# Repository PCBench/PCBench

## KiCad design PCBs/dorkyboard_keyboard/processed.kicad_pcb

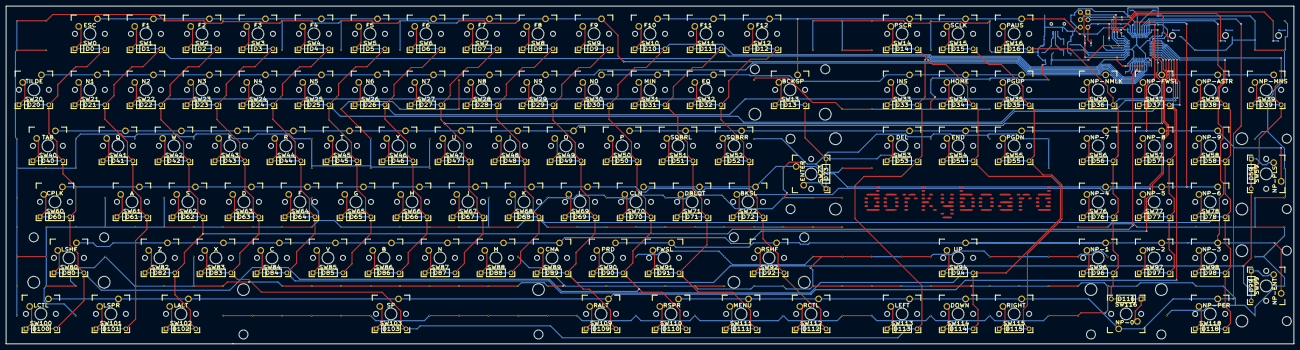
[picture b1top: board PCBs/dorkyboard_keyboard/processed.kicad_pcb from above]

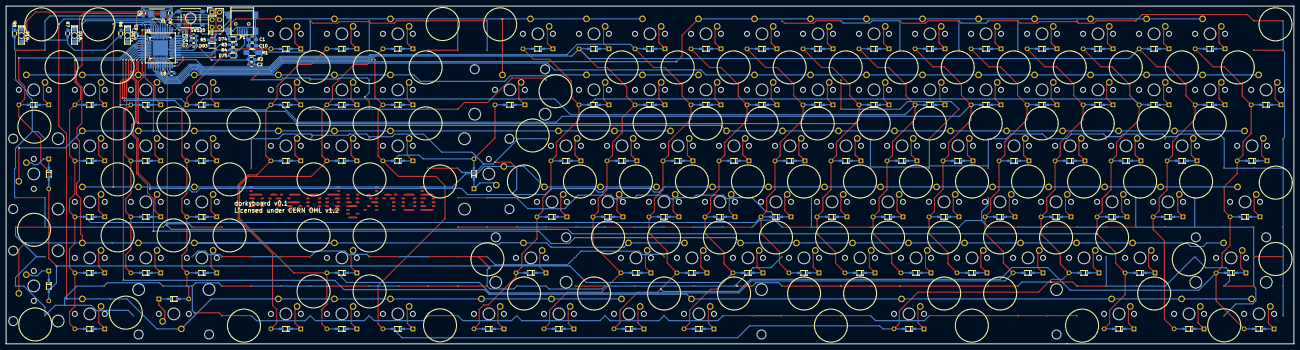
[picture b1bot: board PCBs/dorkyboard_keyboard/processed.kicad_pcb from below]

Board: 2 copper layers, 436.8 x 114.6 mm, 237 parts (29 on the bottom side), 146 nets.

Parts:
C1, C10: 10uF; C_0805_HandSoldering
C2, C3, C4, C8: 100nF; C_0603_HandSoldering
C5, C6: 22pF; C_0603_HandSoldering
C7, C9: 1uF; C_0603_HandSoldering
D0, D1, D2, D3, D4, D5, D6, D7, D8, D9, D10, D11, D12, D13, D14, D15, D16, D20, D21, D22, D23, D24, D25, D26, D27, D28, D29, D30, D31, D32, D33, D34, D35, D36, D37, D38, D39, D40, D41, D42, D43, D44, D45, D46, D47, D48, D49, D50, D51, D52, D53, D54, D55, D56, D57, D58, D59, D60, D61, D62, D63, D64, D65, D66, D67, D68, D69, D70, D71, D72, D73, D76, D77, D78, D80, D82, D83, D84, D85, D86, D87, D88, D89, D90, D91, D92, D94, D96, D97, D98, D99, D100, D101, D102, D103, D109, D110, D111, D112, D113, D114, D115, D116, D118: D_Small; DIODE_TH-SMT
D17, D18, D19: Led_Small; LED Reverse Mount 3.2x1.6mm Dialight
D74, D75: 6.2V; SOD-323_HandSoldering
D93: 1N4148; SOD-323
P1: USB_MiniB; USB_Mini-B
P2: Do Not Populate; Pin_Header_Straight_2x03
R1: 10R Fusible; R_1206_HandSoldering
R2, R5: 10k; R_0603_HandSoldering
R3, R4: 22R; R_0603_HandSoldering
R6, R7, R8: 604R; R_0603_HandSoldering
SW0: ESC; CHERRY_PCB_100H
SW1: F1; CHERRY_PCB_100H
SW2: F2; CHERRY_PCB_100H
SW3: F3; CHERRY_PCB_100H
SW4: F4; CHERRY_PCB_100H
SW5: F5; CHERRY_PCB_100H
SW6: F6; CHERRY_PCB_100H
SW7: F7; CHERRY_PCB_100H
SW8: F8; CHERRY_PCB_100H
SW9: F9; CHERRY_PCB_100H
SW10: F10; CHERRY_PCB_100H
SW11: F11; CHERRY_PCB_100H
SW12: F12; CHERRY_PCB_100H
SW13: BCKSP; CHERRY_PCB_200H
SW14: PSCR; CHERRY_PCB_100H
SW15: SCLK; CHERRY_PCB_100H
SW16: PAUS; CHERRY_PCB_100H
SW20: TILDE; CHERRY_PCB_100H
SW21: N1; CHERRY_PCB_100H
SW22: N2; CHERRY_PCB_100H
SW23: N3; CHERRY_PCB_100H
SW24: N4; CHERRY_PCB_100H
SW25: N5; CHERRY_PCB_100H
SW26: N6; CHERRY_PCB_100H
SW27: N7; CHERRY_PCB_100H
SW28: N8; CHERRY_PCB_100H
SW29: N9; CHERRY_PCB_100H
SW30: N0; CHERRY_PCB_100H
SW31: MIN; CHERRY_PCB_100H
SW32: EQ; CHERRY_PCB_100H
SW33: INS; CHERRY_PCB_100H
SW34: HOME; CHERRY_PCB_100H
SW35: PGUP; CHERRY_PCB_100H
SW36: NP-NMLK; CHERRY_PCB_100H
SW37: NP-FWSL; CHERRY_PCB_100H
SW38: NP-ASTR; CHERRY_PCB_100H
SW39: NP-MNS; CHERRY_PCB_100H
SW40: TAB; CHERRY_PCB_150H
SW41: Q; CHERRY_PCB_100H
SW42: W; CHERRY_PCB_100H
SW43: E; CHERRY_PCB_100H
SW44: R; CHERRY_PCB_100H
SW45: T; CHERRY_PCB_100H
SW46: Y; CHERRY_PCB_100H
SW47: U; CHERRY_PCB_100H
SW48: I; CHERRY_PCB_100H
SW49: O; CHERRY_PCB_100H
SW50: P; CHERRY_PCB_100H
SW51: SQBRL; CHERRY_PCB_100H
SW52: SQBRR; CHERRY_PCB_100H
SW53: DEL; CHERRY_PCB_100H
SW54: END; CHERRY_PCB_100H
SW55: PGDN; CHERRY_PCB_100H
SW56: NP-7; CHERRY_PCB_100H
SW57: NP-8; CHERRY_PCB_100H
SW58: NP-9; CHERRY_PCB_100H
SW59: NP-PLS; CHERRY_PCB_200V
SW60: CPLK; CHERRY_PCB_175H
SW61: A; CHERRY_PCB_100H
SW62: S; CHERRY_PCB_100H
SW63: D; CHERRY_PCB_100H
SW64: F; CHERRY_PCB_100H
SW65: G; CHERRY_PCB_100H
SW66: H; CHERRY_PCB_100H
SW67: J; CHERRY_PCB_100H
SW68: K; CHERRY_PCB_100H
SW69: L; CHERRY_PCB_100H
SW70: CLN; CHERRY_PCB_100H
SW71: DBLQT; CHERRY_PCB_100H
SW72: BKSL; CHERRY_PCB_100H
SW73: ENTER; CHERRY_PCB_ISOR
SW76: NP-4; CHERRY_PCB_100H
SW77: NP-5; CHERRY_PCB_100H
SW78: NP-6; CHERRY_PCB_100H
SW80: LSHF; CHERRY_PCB_225H
SW82: Z; CHERRY_PCB_100H
SW83: X; CHERRY_PCB_100H
SW84: C; CHERRY_PCB_100H
SW85: V; CHERRY_PCB_100H
SW86: B; CHERRY_PCB_100H
SW87: N; CHERRY_PCB_100H
SW88: M; CHERRY_PCB_100H
SW89: CMA; CHERRY_PCB_100H
SW90: PRD; CHERRY_PCB_100H
SW91: FWSL; CHERRY_PCB_100H
SW92: RSHF; CHERRY_PCB_275H
SW94: UP; CHERRY_PCB_100H
SW96: NP-1; CHERRY_PCB_100H
SW97: NP-2; CHERRY_PCB_100H
SW98: NP-3; CHERRY_PCB_100H
SW99: NP-ENT; CHERRY_PCB_200V
SW100: LCTL; CHERRY_PCB_125H
SW101: LSPR; CHERRY_PCB_125H
SW102: LALT; CHERRY_PCB_125H
SW103: SP; CHERRY_PCB_625H
SW109: RALT; CHERRY_PCB_125H
SW110: RSPR; CHERRY_PCB_125H
SW111: MENU; CHERRY_PCB_125H
SW112: RCTL; CHERRY_PCB_125H
SW113: LEFT; CHERRY_PCB_100H
SW114: DOWN; CHERRY_PCB_100H
SW115: RIGHT; CHERRY_PCB_100H
SW116: NP-0; CHERRY_PCB_200H
SW118: NP-PER; CHERRY_PCB_100H
SW120: SW_P; SW_SPST_PTS645
U1: ATMEGA32U4-M; QFN44-7x7mm-QFP-10x10mm
Y1: 16MHz; Crystal_SMD_5032_2Pads

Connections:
+5V: C9.1, D93.1, P2.2, R5.1, U1.2, U1.14, U1.24, U1.34, U1.44
/matrix/Col0: D0.1, D10.1, D20.1, D30.1, D40.1, D50.1, D60.1, D70.1, D80.1, D90.1, D100.1, D110.1, U1.1
/matrix/Col1: D1.1, D11.1, D21.1, D31.1, D41.1, D51.1, D61.1, D71.1, D91.1, D101.1, D111.1, U1.41
/matrix/Col2: D2.1, D12.1, D22.1, D32.1, D42.1, D52.1, D62.1, D72.1, D82.1, D92.1, D102.1, D112.1, U1.40
/matrix/Col3: D3.1, D13.1, D23.1, D33.1, D43.1, D53.1, D63.1, D73.1, D83.1, D103.1, D113.1, U1.39
/matrix/Col4: D4.1, D14.1, D24.1, D34.1, D44.1, D54.1, D64.1, D84.1, D94.1, D114.1, U1.38
/matrix/Col5: D5.1, D15.1, D25.1, D35.1, D45.1, D55.1, D65.1, D85.1, D115.1, U1.29
/matrix/Col6: D6.1, D16.1, D26.1, D36.1, D46.1, D56.1, D66.1, D76.1, D86.1, D96.1, D116.1, U1.28
/matrix/Col7: D7.1, D27.1, D37.1, D47.1, D57.1, D67.1, D77.1, D87.1, D97.1, U1.27
/matrix/Col8: D8.1, D28.1, D38.1, D48.1, D58.1, D68.1, D78.1, D88.1, D98.1, D118.1, U1.26
/matrix/Col9: D9.1, D29.1, D39.1, D49.1, D59.1, D69.1, D89.1, D99.1, D109.1, U1.25
/matrix/LED0: D17.2, U1.8
/matrix/LED1: D18.2, P2.3, U1.9
/matrix/LED2: D19.2, P2.4, U1.10
/matrix/Row0: SW100.1, SW101.1, SW102.1, SW103.1, SW109.1, U1.30
/matrix/Row1: SW110.1, SW111.1, SW112.1, SW113.1, SW114.1, SW115.1, SW116.1, SW118.1, U1.18
/matrix/Row2: SW80.1, SW82.1, SW83.1, SW84.1, SW85.1, SW86.1, SW87.1, SW88.1, SW89.1, U1.31
/matrix/Row3: SW90.1, SW91.1, SW92.1, SW94.1, SW96.1, SW97.1, SW98.1, SW99.1, U1.19
/matrix/Row4: SW60.1, SW61.1, SW62.1, SW63.1, SW64.1, SW65.1, SW66.1, SW67.1, SW68.1, SW69.1, U1.32
/matrix/Row5: SW70.1, SW71.1, SW72.1, SW73.1, SW76.1, SW77.1, SW78.1, U1.20
/matrix/Row6: SW40.1, SW41.1, SW42.1, SW43.1, SW44.1, SW45.1, SW46.1, SW47.1, SW48.1, SW49.1, U1.33
/matrix/Row7: SW50.1, SW51.1, SW52.1, SW53.1, SW54.1, SW55.1, SW56.1, SW57.1, SW58.1, SW59.1, U1.21
/matrix/Row8: SW20.1, SW21.1, SW22.1, SW23.1, SW24.1, SW25.1, SW26.1, SW27.1, SW28.1, SW29.1, U1.36
/matrix/Row9: SW30.1, SW31.1, SW32.1, SW33.1, SW34.1, SW35.1, SW36.1, SW37.1, SW38.1, SW39.1, U1.22
/matrix/Row10: SW0.1, SW1.1, SW2.1, SW3.1, SW4.1, SW5.1, SW6.1, SW7.1, SW8.1, SW9.1, U1.37
/matrix/Row11: SW10.1, SW11.1, SW12.1, SW13.1, SW14.1, SW15.1, SW16.1, U1.12
/microcontroller/MISO: P2.1, U1.11
/microcontroller/RESET: C3.1, C4.1, D93.2, P2.5, R5.2, SW120.2, U1.13
/microcontroller/VUSB: C2.1, R1.2, R2.1, U1.7
GND: C1.2, C2.2, C3.2, C4.2, C5.2, C6.2, C7.2, C8.2, C9.2, C10.2, D74.2, D75.2, P1.5, P1.6, P2.6, R2.2, R6.2, R7.2, R8.2, SW120.1, U1.5, U1.15, U1.23, U1.35, U1.43, U1.45
unnamed: C1.1, C10.1, P1.1, R1.1
unnamed: C5.1, U1.17, Y1.1
unnamed: C6.1, U1.16, Y1.2
unnamed: C7.1, U1.6
unnamed: C8.1, U1.42
unnamed: D0.2, SW0.2
unnamed: D1.2, SW1.2
unnamed: D2.2, SW2.2
unnamed: D3.2, SW3.2
unnamed: D4.2, SW4.2
unnamed: D5.2, SW5.2
unnamed: D6.2, SW6.2
unnamed: D7.2, SW7.2
unnamed: D8.2, SW8.2
unnamed: D9.2, SW9.2
unnamed: D10.2, SW10.2
unnamed: D11.2, SW11.2
unnamed: D12.2, SW12.2
unnamed: D13.2, SW13.2
unnamed: D14.2, SW14.2
unnamed: D15.2, SW15.2
unnamed: D16.2, SW16.2
unnamed: D17.1, R6.1
unnamed: D18.1, R7.1
unnamed: D19.1, R8.1
unnamed: D20.2, SW20.2
unnamed: D21.2, SW21.2
unnamed: D22.2, SW22.2
unnamed: D23.2, SW23.2
unnamed: D24.2, SW24.2
unnamed: D25.2, SW25.2
unnamed: D26.2, SW26.2
unnamed: D27.2, SW27.2
unnamed: D28.2, SW28.2
unnamed: D29.2, SW29.2
unnamed: D30.2, SW30.2
unnamed: D31.2, SW31.2
unnamed: D32.2, SW32.2
unnamed: D33.2, SW33.2
unnamed: D34.2, SW34.2
unnamed: D35.2, SW35.2
unnamed: D36.2, SW36.2
unnamed: D37.2, SW37.2
unnamed: D38.2, SW38.2
unnamed: D39.2, SW39.2
unnamed: D40.2, SW40.2
unnamed: D41.2, SW41.2
unnamed: D42.2, SW42.2
unnamed: D43.2, SW43.2
unnamed: D44.2, SW44.2
unnamed: D45.2, SW45.2
unnamed: D46.2, SW46.2
unnamed: D47.2, SW47.2
unnamed: D48.2, SW48.2
unnamed: D49.2, SW49.2
unnamed: D50.2, SW50.2
unnamed: D51.2, SW51.2
unnamed: D52.2, SW52.2
unnamed: D53.2, SW53.2
unnamed: D54.2, SW54.2
unnamed: D55.2, SW55.2
unnamed: D56.2, SW56.2
unnamed: D57.2, SW57.2
unnamed: D58.2, SW58.2
unnamed: D59.2, SW59.2
unnamed: D60.2, SW60.2
unnamed: D61.2, SW61.2
unnamed: D62.2, SW62.2
unnamed: D63.2, SW63.2
unnamed: D64.2, SW64.2
unnamed: D65.2, SW65.2
unnamed: D66.2, SW66.2
unnamed: D67.2, SW67.2
unnamed: D68.2, SW68.2
unnamed: D69.2, SW69.2
unnamed: D70.2, SW70.2
unnamed: D71.2, SW71.2
unnamed: D72.2, SW72.2
unnamed: D73.2, SW73.2
unnamed: D74.1, P1.3, R3.1
unnamed: D75.1, P1.2, R4.1
unnamed: D76.2, SW76.2
unnamed: D77.2, SW77.2
unnamed: D78.2, SW78.2
unnamed: D80.2, SW80.2
unnamed: D82.2, SW82.2
unnamed: D83.2, SW83.2
unnamed: D84.2, SW84.2
unnamed: D85.2, SW85.2
unnamed: D86.2, SW86.2
unnamed: D87.2, SW87.2
unnamed: D88.2, SW88.2
unnamed: D89.2, SW89.2
unnamed: D90.2, SW90.2
unnamed: D91.2, SW91.2
unnamed: D92.2, SW92.2
unnamed: D94.2, SW94.2
unnamed: D96.2, SW96.2
unnamed: D97.2, SW97.2
unnamed: D98.2, SW98.2
unnamed: D99.2, SW99.2
unnamed: D100.2, SW100.2
unnamed: D101.2, SW101.2
unnamed: D102.2, SW102.2
unnamed: D103.2, SW103.2
unnamed: D109.2, SW109.2
unnamed: D110.2, SW110.2
unnamed: D111.2, SW111.2
unnamed: D112.2, SW112.2
unnamed: D113.2, SW113.2
unnamed: D114.2, SW114.2
unnamed: D115.2, SW115.2
unnamed: D116.2, SW116.2
unnamed: D118.2, SW118.2
unnamed: R3.2, U1.4
unnamed: R4.2, U1.3

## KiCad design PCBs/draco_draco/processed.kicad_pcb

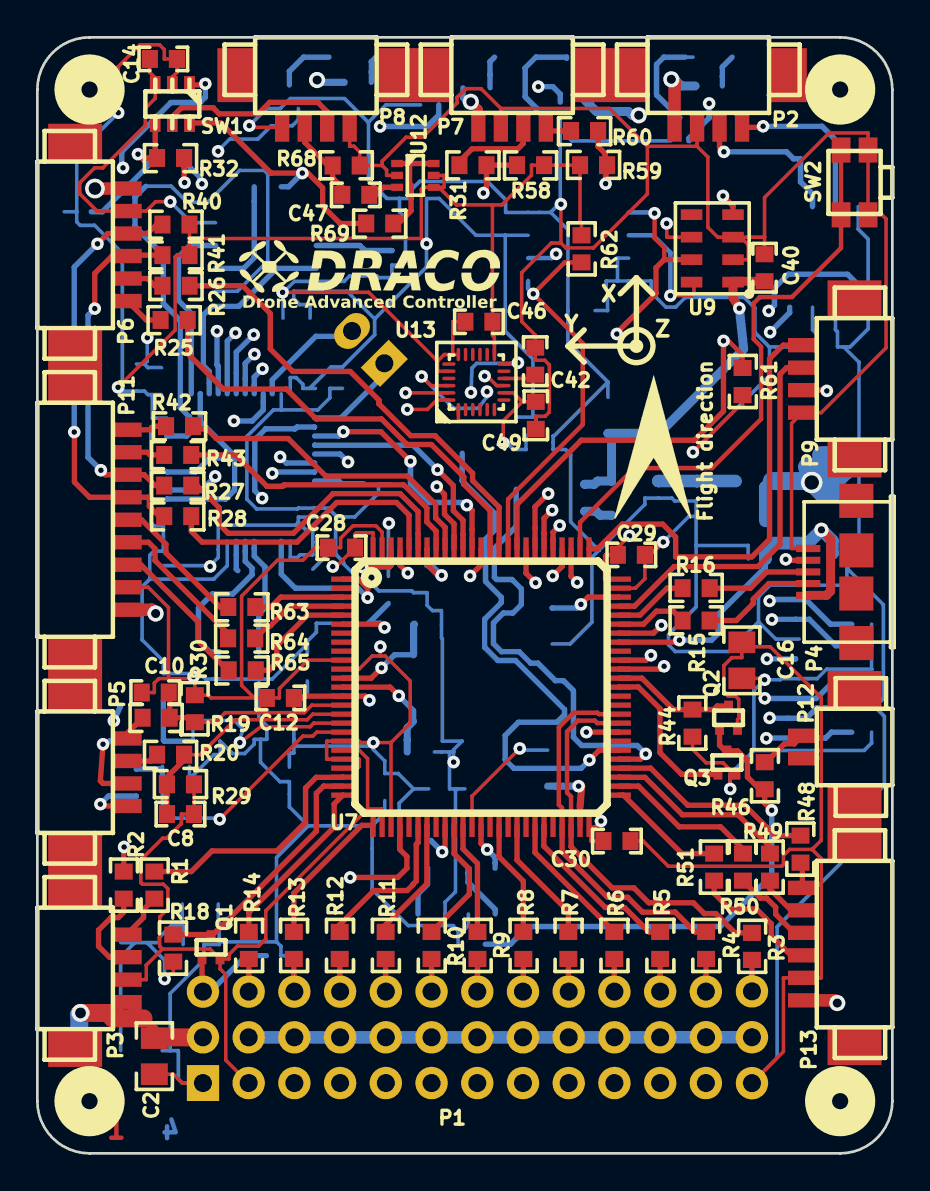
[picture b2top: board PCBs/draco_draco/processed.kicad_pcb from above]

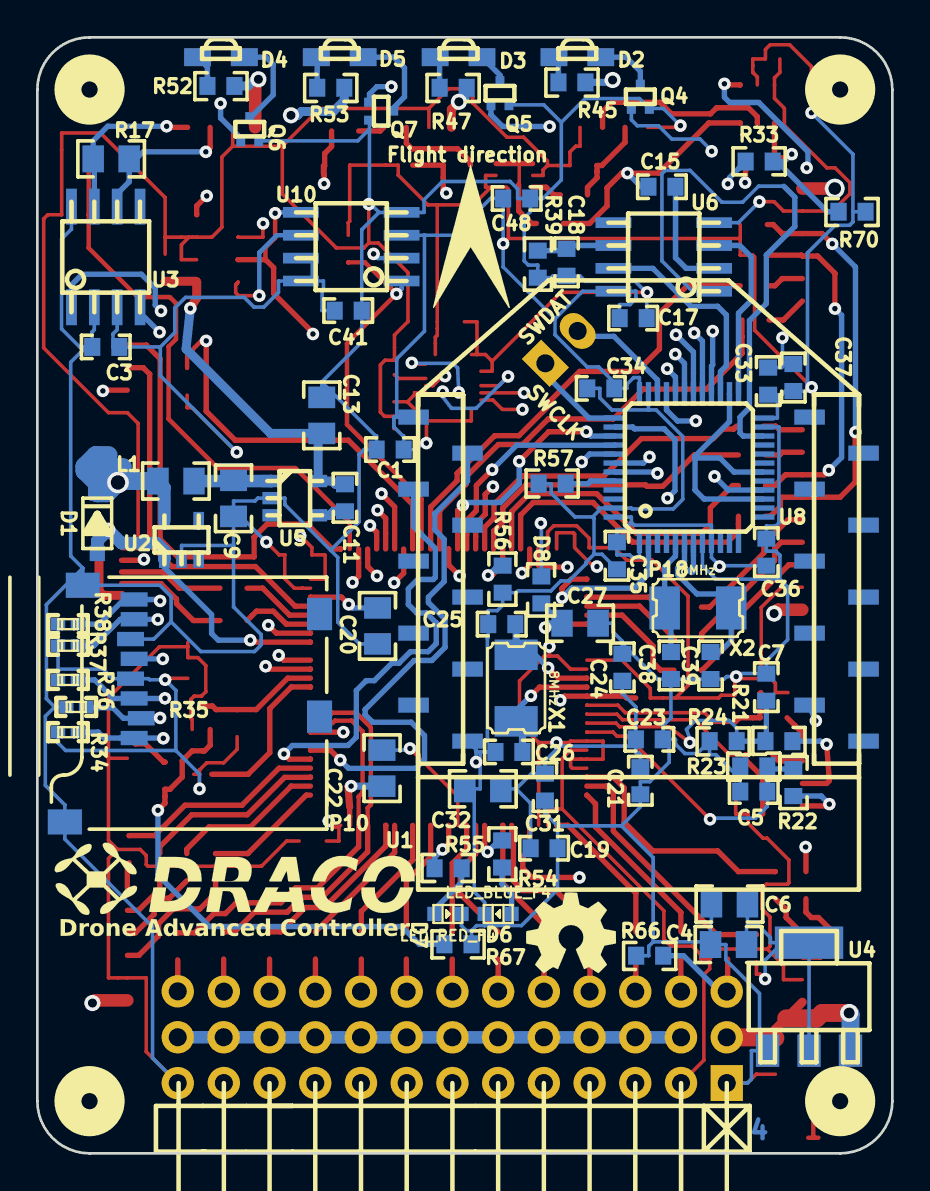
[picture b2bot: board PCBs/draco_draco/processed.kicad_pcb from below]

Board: 4 copper layers, 47.5 x 62.0 mm, 172 parts (83 on the bottom side), 154 nets.

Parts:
C1, C3, C5, C7, C8, C10, C12, C14, C15, C17, C19, C21, C23, C24, C28, C29, C30, C33, C34, C35, C36, C40, C41, C42, C46, C47, C48: 100nF; c_0603
C2, C4, C32: 4.7uF; c_0805
C6, C13, C27: 10uF; c_0805
C9: 1uF; c_0805
C11, C49: 10nF; c_0603
C16: 22uF; c_0805
C18: 56nF; c_0603
C20, C22: 2.2uF; c_0805
C25, C26, C38, C39: 18pF; c_0603
C31: 1uF; c_0603
C37: 4.7uF; c_0603
D1: PMEG6010CEH; sod123
D2: LED_RED; led_2.1x0.6
D3: LED_ORANGE; led_2.1x0.6
D4: LED_BLUE; led_2.1x0.6
D5: LED_GREEN; led_2.1x0.6
D6: LED_BLUE_F4; Led_0603
D7: LED_RED_F4; Led_0603
D8: CD0603-S01575; r_0603
G1, G3: DUMMY; ARROW
G2, G4: DUMMY; LOGOGO
G5: DUMMY; Logo_silk_OSHW_6x6mm
L1: 10uH; r_0805
P1: CONN_13X3; pin_strip_13x3-90
P2, P3, P5, P7, P8, P9: CONN_4; picoblade_4-90
P4: MICROUSB; conn_usb_B_micro_smd-FCI
P6, P13: CONN_6; picoblade_6-90
P10: MICROSD; MICRO-SD-SOCKET-PP
P11: CONN_9; picoblade_9-90
P12: CONN_2; picoblade_2-90
P14: CONN_2; pin_strip_2
P18: CONN_1; testpoint_pad
P19, P20, P21, P22: CONN_1; 1pin
Q1, Q2: NTA4153NT1G; sc75
Q3: NTA4151PT1G; sc75
Q4, Q5, Q6, Q7: PDTC114EE; sc75
R1, R2, R3, R4, R5, R6, R7, R8, R9, R10, R11, R12, R13, R14, R25, R26, R33, R42, R43, R46, R48, R49, R50, R51, R63, R64, R65: 470R; r_0603
R15, R16: 22R; r_0603
R17: 120R; r_0805
R18, R44, R58, R59: 4k7; r_0603
R19, R20, R21, R24, R29, R30, R56, R57, R61, R62, R66, R67: 39k; r_0603
R22: 82k; r_0603
R23: 12k; r_0603
R27, R28, R31, R32, R53, R60, R70: 220R; r_0603
R34, R36, R37, R38: 39k; r_0402
R35: 1M; r_0402
R39: 681k; r_0603
R40, R41: 4.7k; r_0603
R45, R47, R55: 330R; r_0603
R52: 180R; r_0603
R54: 100R; r_0603
R68, R69: 75R; r_0603
SW1: STG719; sot23-6
SW2: EVQP7A01K; EVQP7J01K
U1: XBEE; xbee-smt
U2: LTC4411; sot23-5
U3: SN65HVD233; so-8
U4: ADP3338AKCZ-3.3; stabil_sot223_1
U5: LT1761-3.3; tsot-5
U6: EL1883; so-8
U7: STM32F427VIT6; TQFP-100
U8: STM32F303CC; lqfp48
U9: MS5611
U10: FLASH-SPI-SO8; so-8
U12: MAX4090; sc70-6_2
U13: MPU-9250; dandys_qfn24-3x3
X1, X2: 8MHz; crystal_smd_5x3.2mm

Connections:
+3.3V: C1.2, C3.1, C4.1, C6.1, C14.2, C16.1, C17.2, C19.1, C21.1, C23.1, C24.1, C28.1, C29.1, C30.1, C31.1, C32.1, C33.2, C34.2, C35.2, C36.2, C37.2, C41.1, C46.1, C48.1, C49.1, D8.1, P10.4, Q3.2, R18.2, R34.2, R36.2, R37.2, R38.2, R40.2, R41.2, R44.2, R58.2, R59.2, R61.1, R62.2, R70.2, SW1.2, U1.1, U3.3, U4.OUT, U6.8, U7.11, U7.19, U7.21, U7.22, U7.28, U7.50, U7.75, U7.100, U8.1, U8.9, U8.24, U8.36, U8.48, U10.3, U10.7, U10.8, U12.4, U12.5, U13.1, U13.8, U13.13
+3.3VADC: C11.1, C13.1, C40.1, U5.5, U9.1
+5V: C2.1, D1.2, L1.1, P1.2, P1.5, P1.8, P1.11, P1.14, P1.17, P1.20, P1.23, P1.26, P1.29, P1.32, P1.35, P1.38, P2.4, P3.4, P6.1, P7.4, P11.9, P13.1, R45.2, R47.2, R52.2, R53.2, U2.5, U4.IN
AD0: C5.2, R22.2, R23.2, U7.18
AD1: C7.2, R21.2, R24.2, U7.17
AD2: C8.2, R20.2, R29.2, U7.16
AD3: C10.2, R19.2, R30.2, U7.15
CAN_RX: U3.4, U7.81
CAN_TX: U3.1, U7.82
EXTGPIO1: R65.2, U7.5
EXTGPIO2: R64.2, U7.4
EXTGPIO3: R63.2, U7.3
EXTI2C_SCL: R27.2, U7.95
EXTI2C_SDA: R28.2, U7.96
EXTSPI_CS: R51.1, U7.51
EXTSPI_MISO: R49.1, U7.53
EXTSPI_MOSI: R48.1, U7.54
EXTSPI_SCK: R50.1, U7.52
EXTUART1_RX: R43.2, U7.93
EXTUART1_TX: R42.2, U7.92
EXTUART2_RX: R31.2, R58.1, U8.43
EXTUART2_TX: R59.1, R60.2, U8.42
F3_CS: U7.98, U8.38
F3_INT: U7.1, U8.2
F4_NRST: C12.2, P9.2, U7.14
F4_SWCLK: P9.4, U7.76
F4_SWDIO: P9.3, U7.72
FLASH_CS: R62.1, U7.85, U10.1
GND: C1.1, C2.2, C3.2, C4.2, C5.1, C6.2, C7.1, C8.1, C9.2, C10.1, C12.1, C13.2, C14.1, C16.2, C17.1, C18.1, C19.2, C20.2, C21.2, C22.2, C23.2, C24.2, C25.2, C26.2, C27.2, C28.2, C29.2, C30.2, C31.2, C32.2, C33.1, C34.1, C35.1, C36.1, C37.1, C38.2, C39.2, C40.2, C41.2, C42.2, C46.2, C48.2, C49.2, D6.2, D7.2, P1.1, P1.4, P1.7, P1.10, P1.13, P1.16, P1.19, P1.22, P1.25, P1.28, P1.31, P1.34, P1.37, P2.3, P3.3, P4.5, P6.2, P7.3, P8.1, P8.4, P9.1, P10.6, P10.GND, P11.8, P12.1, P13.2, Q1.2, Q2.2, Q4.2, Q5.2, Q6.2, Q7.2, R23.1, R24.1, R29.1, R30.1, R35.1, R39.1, R56.2, R57.2, R66.1, R67.2, R68.1, SW1.3, SW2.1, U1.10, U2.2, U3.2, U3.8, U4.GND, U5.2, U6.4, U7.10, U7.20, U7.27, U7.37, U7.74, U7.99, U8.8, U8.23, U8.35, U8.47, U9.2, U9.3, U10.4, U12.2, U13.18, U13.20
GPS_RX: R25.2, U7.87
GPS_TX: R26.2, U7.86
LED_BLUE: Q6.1, U8.33
LED_GREEN: Q7.1, U8.32
LED_ORANGE: Q5.1, U8.31
LED_RED: Q4.1, U8.30
MPU_CS: U7.88, U13.22
MPU_INT: U7.97, U13.12
MS_CS: R61.2, U7.84, U9.4
unnamed: C20.1, U7.73
unnamed: C22.1, U7.49
unnamed: C27.1, D8.2, U7.6
unnamed: R57.1, U8.44
unnamed: P18.1, U8.7
unnamed: C38.1, U8.5, X2.2
unnamed: R55.2, U7.38
unnamed: SW2.2, U7.77
unnamed: R56.1, U7.94
unnamed: P14.2, U8.34
unnamed: D7.1, R55.1
unnamed: C42.1, U13.10
unnamed: R54.2, U7.34
unnamed: D6.1, R54.1
unnamed: P14.1, U8.37
unnamed: C39.1, U8.6, X2.1
unnamed: C25.1, U7.12, X1.2
unnamed: C26.1, U7.13, X1.1
unnamed: D3.2, Q5.3
unnamed: D2.2, Q4.3
unnamed: P11.6, R64.1
unnamed: D5.2, Q7.3
unnamed: D4.2, Q6.3
unnamed: P7.2, R31.1
unnamed: P7.1, R60.1
unnamed: C15.1, R69.1, SW1.6
unnamed: R69.2, U12.1, U12.6
unnamed: R32.1, R33.1, R70.1, SW1.4
unnamed: P8.2, SW1.5
unnamed: P1.3, Q1.1, R66.2
unnamed: C47.2, P8.3, R68.2
unnamed: C47.1, U12.3
unnamed: P5.1, R19.1
unnamed: P5.2, R20.1
unnamed: P11.7, R65.1
unnamed: P11.5, R63.1
unnamed: P11.2, R43.1
unnamed: P11.1, R42.1
unnamed: P5.4, R22.1
unnamed: P5.3, R21.1
unnamed: C11.2, U5.4
unnamed: P6.4, P11.3, R27.1, R41.1
unnamed: P6.3, P11.4, R28.1, R40.1
unnamed: P6.6, R25.1
unnamed: P6.5, R26.1
unnamed: C9.1, L1.2, U5.1
unnamed: P4.3, R16.1
unnamed: P4.2, R15.1
unnamed: P3.1, R1.1
unnamed: P3.2, R2.1
unnamed: P2.1, R17.2, U3.7
unnamed: P2.2, R17.1, U3.6
unnamed: P1.6, R14.1
unnamed: P13.3, R51.2
unnamed: C18.2, R39.2, U6.6
unnamed: C15.2, U6.2
unnamed: P1.15, R11.1
unnamed: P1.12, R12.1
unnamed: P1.9, R13.1
unnamed: P1.39, R3.1
unnamed: P1.36, R4.1
unnamed: P1.27, R7.1
unnamed: P1.33, R5.1
unnamed: P1.30, R6.1
unnamed: P1.24, R8.1
unnamed: P1.21, R9.1
unnamed: P1.18, R10.1
unnamed: P12.2, R46.2
unnamed: Q2.1, Q3.3, R46.1, R67.1
unnamed: D5.1, R53.1
unnamed: D4.1, R52.1
unnamed: D3.1, R47.1
unnamed: P13.6, R48.2
unnamed: P13.5, R49.2
unnamed: P13.4, R50.2
unnamed: D2.1, R45.1
OSD_CSYNC: U6.1, U8.22
OSD_HSYNC: U6.7, U8.27
OSD_MISO_MASK: SW1.1, U8.16
OSD_MOSI_VOUT: R32.2, U8.28
OSD_PIXEL_CLOCK: U8.15, U8.18, U8.26
OSD_SYNCOUT: R33.2, U8.29
OSD_VSYNC: U6.3, U8.25
PWM1: R14.2, U7.25
PWM2: R13.2, U7.26
PWM3: R12.2, U7.31
PWM4: R11.2, U7.32
PWM5: R10.2, U7.35
PWM6: R9.2, U7.36
PWM7: R8.2, U7.40
PWM8: R7.2, U7.42
PWM9: R6.2, U7.44
PWM10: R5.2, U7.45
PWM11: R4.2, U7.47, U7.60
PWM12: R3.2, U7.48, U7.59
SBUS: Q1.3, R18.1, U7.24
SDIO_CLK: P10.5, U7.80
SDIO_CMD: P10.3, R36.1, U7.83
SDIO_D0: P10.7, R37.1, U7.65
SDIO_D1: P10.8, R38.1, U7.66
SDIO_D2: P10.1, R34.1, U7.78
SDIO_D3: P10.2, R35.2, U7.79
SON_ECHO: R1.2, U7.23
SON_TRIG: R2.2, U7.29
SPI_MISO: U7.90, U8.40, U9.6, U10.2, U13.9
SPI_MOSI: U7.91, U8.41, U9.7, U10.5, U13.24
SPI_SCK: U7.89, U8.39, U9.8, U10.6, U13.23
SPORT_RX: Q2.3, R44.1, U7.64
SPORT_TX: Q3.1, U7.63
USBDM: R15.2, U7.70
USBDP: R16.2, U7.71
USBVB: D1.1, P4.1, U2.1, U7.68
USB_ID: P4.4, U7.69
XBEE_CTS: U1.12, U7.58
XBEE_RX: U1.2, U7.56
XBEE_TX: U1.3, U7.55

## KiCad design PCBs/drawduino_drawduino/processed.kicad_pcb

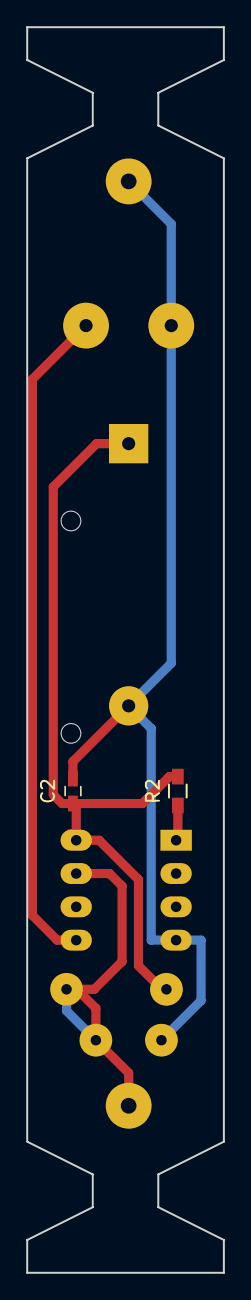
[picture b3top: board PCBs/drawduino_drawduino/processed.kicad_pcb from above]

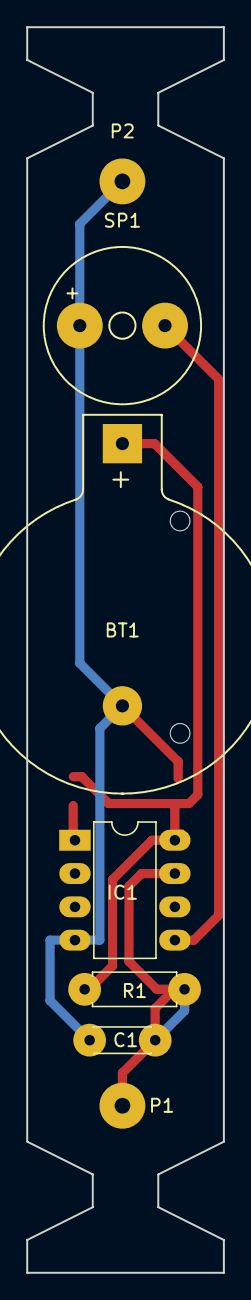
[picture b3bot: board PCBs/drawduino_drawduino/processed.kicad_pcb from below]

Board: 2 copper layers, 15.0 x 95.0 mm, 9 parts (7 on the bottom side), 5 nets.

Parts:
BT1: Battery; Keystone_103_1x20mm-CoinCell
C1: C; C_Disc_D4.3mm_W1.9mm_P5.00mm
C2: C; C_0603_HandSoldering
IC1: ATTINY85-P; DIP-8_W7.62mm_LongPads
P1, P2: CONN_01X01; SolderWirePad_single_1-2mmDrill
R1: R; R_Axial_DIN0207_L6.3mm_D2.5mm_P7.62mm_Horizontal
R2: R; R_0603_HandSoldering
SP1: SPEAKER; Buzzer_12x9.5RM7.6

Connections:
GND: BT1.2, C1.2, C2.2, IC1.4, P2.1, SP1.1
unnamed: C1.1, IC1.7, P1.1, R1.1
unnamed: IC1.1, R2.1
unnamed: IC1.5, SP1.2
VCC: BT1.1, C2.1, IC1.8, R1.2, R2.2

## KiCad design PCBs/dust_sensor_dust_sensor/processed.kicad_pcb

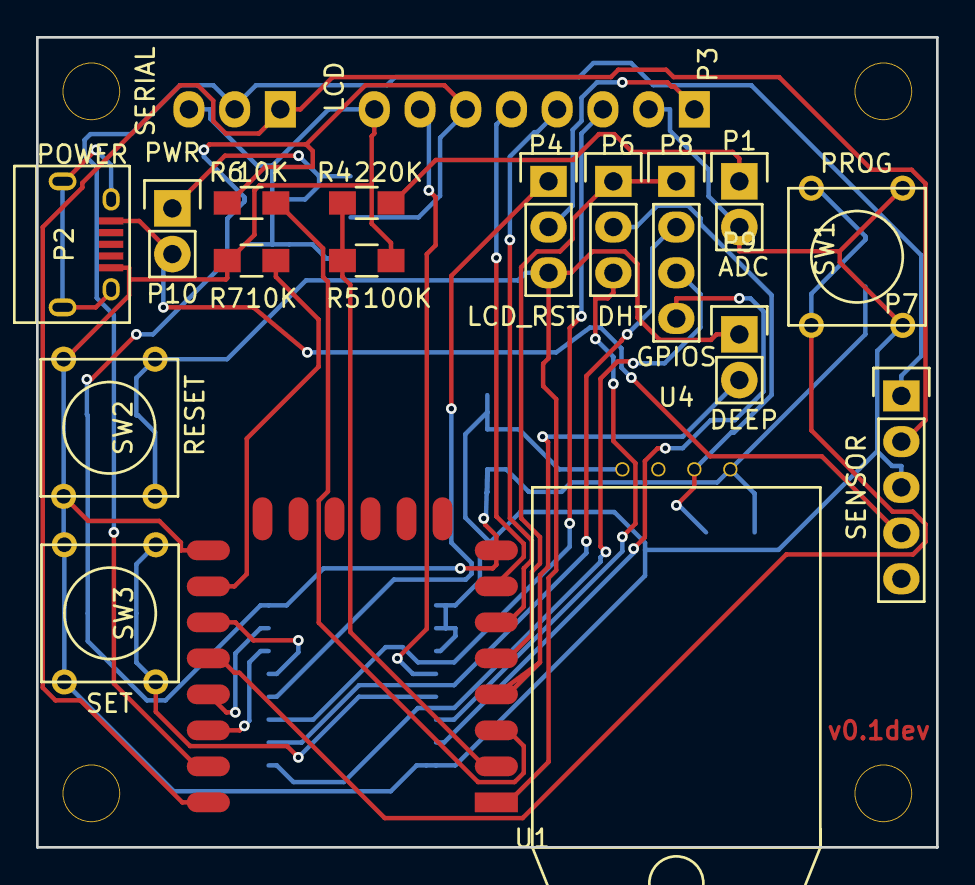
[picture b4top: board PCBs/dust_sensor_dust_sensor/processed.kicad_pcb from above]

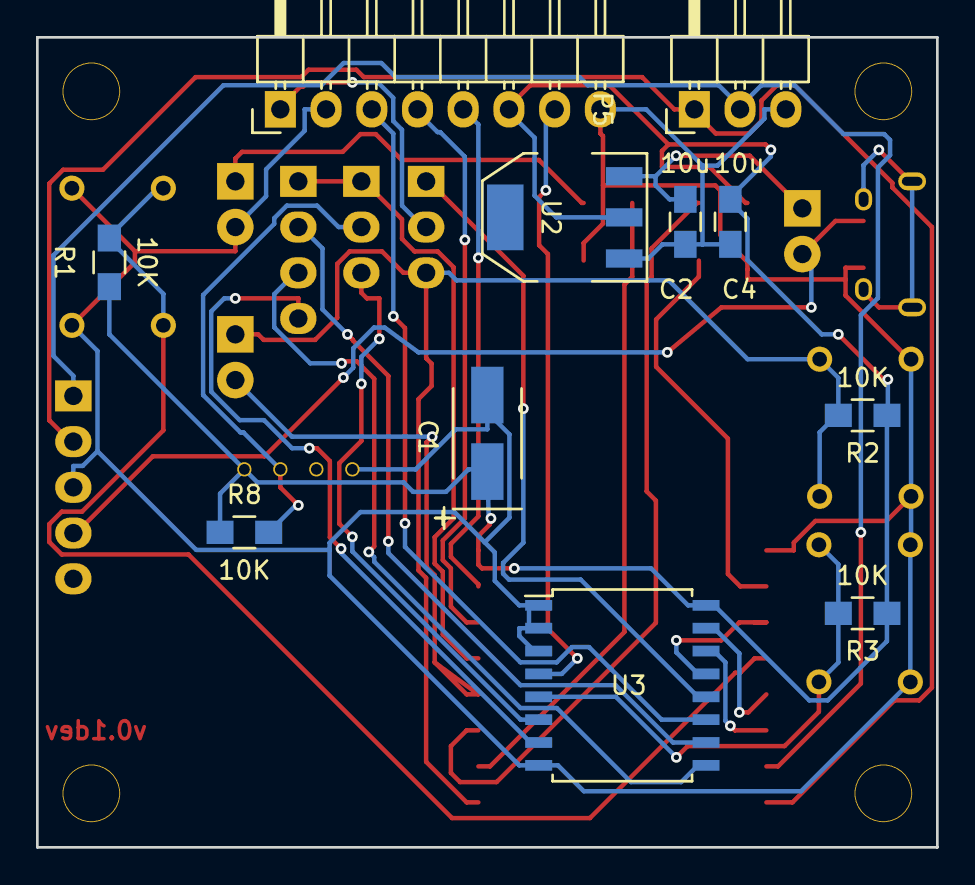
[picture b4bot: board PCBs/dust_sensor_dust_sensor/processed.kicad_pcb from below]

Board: 2 copper layers, 50.0 x 45.0 mm, 32 parts (11 on the bottom side), 29 nets.

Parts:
C1: 100u; TantalC_SizeB_EIA-3528_HandSoldering
C2, C4: 10u; C_0805_HandSoldering
Noname_1, Noname_2, Noname_3, Noname_4: hole_3mm
P1: ADC; Pin_Header_Straight_1x02
P2: POWER; USB_Micro-B
P3: LCD; Pin_Header_Angled_1x08
P4: LCD_RST; Pin_Header_Straight_1x03
P5: SERIAL; Pin_Header_Angled_1x03
P6: DHT; Pin_Header_Straight_1x03
P7: SENSOR; Pin_Header_Straight_1x05
P8: GPIOS; Pin_Header_Straight_1x04
P9: DEEP; Pin_Header_Straight_1x02
P10: PWR; Pin_Header_Straight_1x02
R1, R2, R3, R6, R7, R8: 10K; R_0805_HandSoldering
R4: 220K; R_0805_HandSoldering
R5: 100K; R_0805_HandSoldering
SW1: PROG; SW_PUSH_SMALL
SW2: RESET; SW_PUSH_SMALL
SW3: SET; SW_PUSH_SMALL
U1: ESP-12E
U2: AP1117; SOT-223
U3: PCF8574; SOIC-16_7.5x10.3mm_Pitch1.27mm
U4: DHT22; DHT22_nohole

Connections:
+3V3: C1.1, C4.1, P3.6, R1.1, R2.1, R3.1, R6.2, R8.1, U1.8, U2.2, U3.16, U4.1
+5V: P2.1, P7.4, P10.2
ADC: R4.2, R5.1, U1.2
DHT_EXT: P6.3, U3.6
DHT_GPIO: P6.1, P8.1, U1.5
GND: C1.2, C2.2, C4.2, P1.2, P2.5, P3.2, P3.8, P5.3, P7.3, R5.2, R7.2, SW1.2, SW2.2, SW3.2, U1.15, U2.1, U3.1, U3.2, U3.3, U3.8, U4.4
GPIO16: P9.2, U1.4
LIGHT: P3.7, U3.4
unnamed: C2.1, P10.1, U2.3
unnamed: P1.1, R4.1
unnamed: P3.1, P4.2
unnamed: P3.3, U3.11
unnamed: P3.4, U1.6
unnamed: P3.5, U1.7
unnamed: P4.1, U3.12
unnamed: P6.2, R8.2, U4.2
unnamed: R6.1, U1.3
unnamed: R7.1, U1.16
unnamed: U1.17, U3.13
unnamed: U1.19, U3.15
unnamed: U1.20, U3.14
P3: P8.4, U3.7
P4: P8.3, U3.9
P5: P8.2, U3.10
PROG: R1.2, SW1.1, U1.18
RESET: P4.3, P9.1, R2.2, SW2.1, U1.1
RX: P5.2, P7.1, U1.21
SET: R3.2, SW3.1, U3.5
TX: P5.1, P7.2, U1.22

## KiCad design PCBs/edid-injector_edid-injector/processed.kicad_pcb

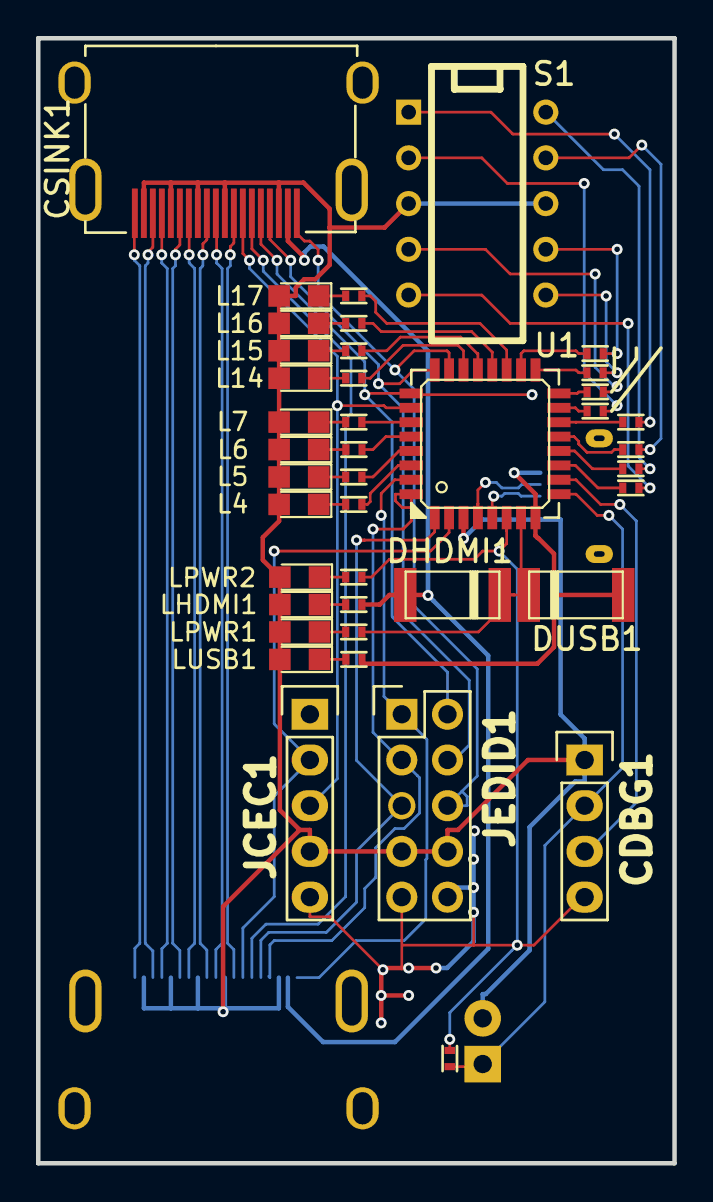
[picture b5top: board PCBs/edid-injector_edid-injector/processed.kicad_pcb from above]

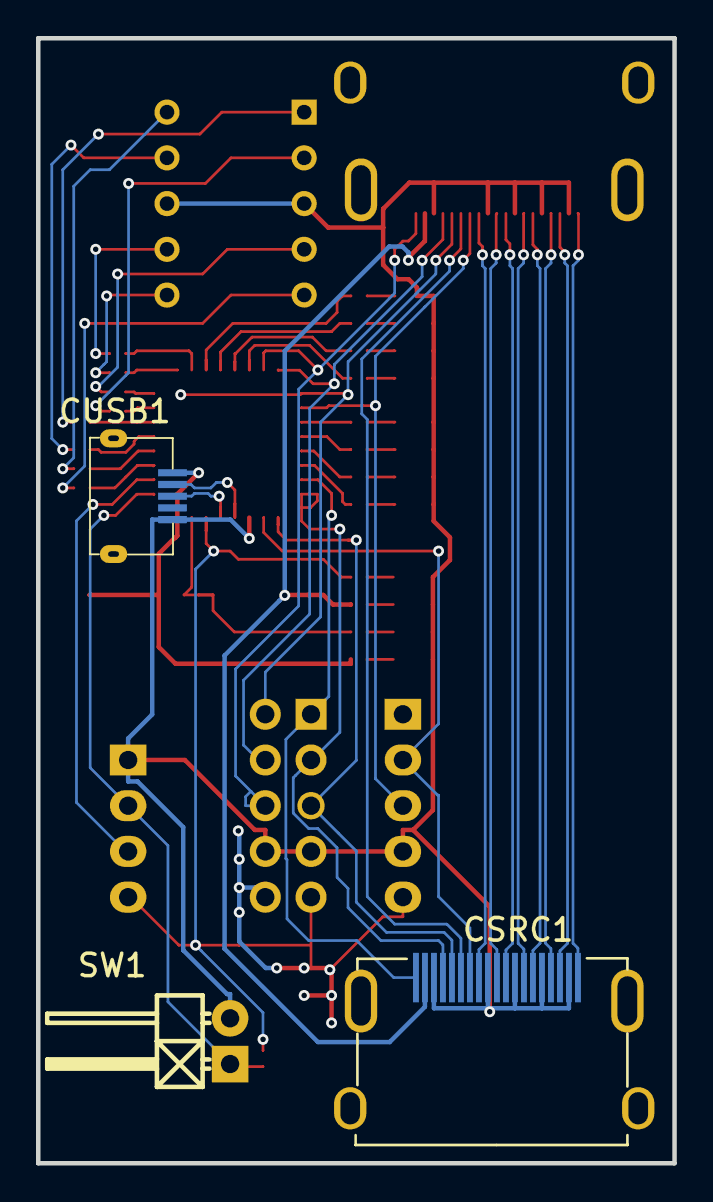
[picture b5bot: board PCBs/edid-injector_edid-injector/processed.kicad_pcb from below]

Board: 2 copper layers, 35.3 x 62.5 mm, 44 parts (3 on the bottom side), 62 nets.

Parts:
CDBG1: CONN_01X04; Pin_Header_Straight_1x04
CSINK1: HDMI; hdmi
CSRC1: HDMI; hdmi
CUSB1: USB-MINI-B2; micro-usb
DHDMI1: DIODE; sod323
DUSB1: DIODE; sod323
JCEC1: CONN_01X05; Pin_Header_Straight_1x05
JEDID1: CONN_02X05; Pin_Header_Straight_2x05
L4, L5, L6, L7, L14, L15, L16, L17: LED; LED_0805
LHDMI1: LED; LED_0805
LPWR1, LPWR2: LED; LED_0805
LUSB1: LED; LED_0805
RHDMI1: R; R_0402
RL4, RL5, RL6, RL7, RL14, RL15, RL16, RL17: R; R_0402
RPWR1, RPWR2: R; R_0402
RRST1: R; R_0402
RSEGA1: R; R_0402
RSEGB1: R; R_0402
RSEGC1: R; R_0402
RSEGD1: R; R_0402
RSEGE1: R; R_0402
RSEGF1: R; R_0402
RSEGG1: R; R_0402
RSEGP1: R; R_0402
RUSB1: R; R_0402
S1: 7SEGM; DIP-10__300
SW1: SW_PUSH; Pin_Header_Angled_1x02
U1: C8051F381/3/5/7/C-GQ; lqfp32

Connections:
/CLK+: CSINK1.10, CSRC1.10
/CLK-: CSINK1.12, CSRC1.12
/D0+: CSINK1.7, CSRC1.7
/D0-: CSINK1.9, CSRC1.9
/D1+: CSINK1.4, CSRC1.4
/D1-: CSINK1.6, CSRC1.6
/D2+: CSINK1.1, CSRC1.1
/D2-: CSINK1.3, CSRC1.3
/D+: CUSB1.2, U1.4
/D-: CUSB1.3, U1.5
/RES: CSINK1.14, CSRC1.14
/SINK_CEC: CSINK1.13, JCEC1.3, U1.26
/SINK_HPD: CSINK1.19, JEDID1.6, U1.23
/SINK_SCL: CSINK1.15, JEDID1.2, U1.25
/SINK_SDA: CSINK1.16, JEDID1.4, U1.24
/SRC_CEC: CSRC1.13, JCEC1.2, U1.2
/SRC_HPD: CSRC1.19, JEDID1.1, U1.31
/SRC_SCL: CSRC1.15, JEDID1.5, U1.1
/SRC_SDA: CSRC1.16, JEDID1.3, U1.32
/VCC3V3: CDBG1.4, JCEC1.5, JEDID1.9, JEDID1.10, RPWR2.2, RRST1.2, U1.6
/VCC5V0: DHDMI1.2, DUSB1.2, RPWR1.1, U1.7
/VHDMI: CSINK1.18, CSRC1.18, DHDMI1.1, RHDMI1.2
/VUSB: CUSB1.1, DUSB1.1, RUSB1.2, U1.8
GND: CDBG1.1, CSINK1.2, CSINK1.5, CSINK1.8, CSINK1.11, CSINK1.17, CSRC1.2, CSRC1.5, CSRC1.8, CSRC1.11, CSRC1.17, CUSB1.5, JCEC1.4, JEDID1.7, JEDID1.8, L4.2, L5.2, L6.2, L7.2, L14.2, L15.2, L16.2, L17.2, LHDMI1.2, LPWR1.2, LPWR2.2, LUSB1.2, S1.3, S1.8, SW1.2, U1.3
unnamed: CDBG1.2, RRST1.1, SW1.1, U1.9
unnamed: CDBG1.3, U1.10
unnamed: L4.1, RL4.2
unnamed: L5.1, RL5.2
unnamed: L6.1, RL6.2
unnamed: L7.1, RL7.2
unnamed: L14.1, RL14.2
unnamed: L15.1, RL15.2
unnamed: L16.1, RL16.2
unnamed: L17.1, RL17.2
unnamed: LHDMI1.1, RHDMI1.1
unnamed: LPWR1.1, RPWR1.2
unnamed: LPWR2.1, RPWR2.1
unnamed: LUSB1.1, RUSB1.1
unnamed: RL4.1, U1.30
unnamed: RL5.1, U1.29
unnamed: RL6.1, U1.28
unnamed: RL7.1, U1.27
unnamed: RL14.1, U1.22
unnamed: RL15.1, U1.21
unnamed: RL16.1, U1.20
unnamed: RL17.1, U1.19
unnamed: RSEGA1.1, U1.18
unnamed: RSEGA1.2, S1.7
unnamed: RSEGB1.1, U1.17
unnamed: RSEGB1.2, S1.6
unnamed: RSEGC1.1, U1.16
unnamed: RSEGC1.2, S1.4
unnamed: RSEGD1.1, U1.15
unnamed: RSEGD1.2, S1.2
unnamed: RSEGE1.1, U1.14
unnamed: RSEGE1.2, S1.1
unnamed: RSEGF1.1, U1.13
unnamed: RSEGF1.2, S1.9
unnamed: RSEGG1.1, U1.12
unnamed: RSEGG1.2, S1.10
unnamed: RSEGP1.1, U1.11
unnamed: RSEGP1.2, S1.5

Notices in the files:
PCBs/dorkyboard_keyboard/processed.kicad_pcb:
Licensed under CERN OHL v1.2
